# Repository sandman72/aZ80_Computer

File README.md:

# aZ80_Computer

#### Was ist der aZ80 Retro Computer?

Die Idee war: Wir bauen einen kleinen bezahlbaren Retro Computer für Workshops im Attraktor e.V.

 - Mit Steckkarten, damit man ihn erweitern kann. 
 - Beim Aufbau jeder Karte gibt es einen Einblick, was diese im Detail macht und wie sie funktioniert
 - Eine Einführung zur Computertechnik der 70er Jahre und die Gedankengänge und Evolutionen, die es zu der Zeit gab.
 - Wir programmieren auf dem aZ80 mit MS-BASIC und Assembler, z.B. kleine Spiele und Programme.

Unter Docs findet sich eine erste Präsentation über das Projekt. Eine ausführliche Anleitung folgt nach den ersten Workshops.

#### Hardware

Die Entscheidung was für ein System ich "neu" entwickeln wollte, fiel auf einen Bauvorschlag von <a href="http://searle.wales/">Grant Searle</a>, 
der auch bei einigen anderen Retro-Computern (z.B. RC2014) zum Einsatz kam. Damit gibt es eine gewisse 
Kompatibilität zum RC2014 System und den Steckkarten, aber der aZ80 sollte als Open-Hardware und -Software verfügbar 
sein und nicht hinter einer Paywall liegen, teure Kits oder Zusatz Hardware benötigen, z.B. wie der RC2014.

#### Software

Für den aZ80 wurden eine alte Version von MS Basic (Nascom Basic 4.7) und der Efex Monitor (Efex V4 1.0) mit einem eigenen BIOS kombiniert.
Das BIOS checkt, ob die wichtigsten Karten des Systems funktionieren und initialisiert diese. Danach erscheint über die serielle Schnittstelle
die Auswahlmöglichkeit zwischen dem Basic und dem Monitor Programm. Diese sind so angepasst, dass sie mit dem 
Online Z80 Compiler <a href="https://www.asm80.com/">ASM80</a> bearbeitet werden können.

Nascom Basic Verweis: <a href="https://gitlab.com/feilipu/NASCOM_BASIC"> https://gitlab.com/feilipu/NASCOM_BASIC </a>

Efex V4 1.0 Verweis: <a href="https://mkpeker.wixsite.com/efex"> https://mkpeker.wixsite.com/efex </a>

#### VDP

Als Highlight hat der aZ80 ein Video Display Prozessor mit an Board, der die Verbindung in die jetzige Zeit herstellt. Mit dieser Karte kann man den aZ80
an einen DVI/HDMI Monitor anschließen und per USB auch Tastatur, Maus, Joystick und/oder Speicher anschließen. Das kombiniert mit einem schicken Gehäuse
mit eingebautem Display gibt dann einen kleinen feinen Standalone Z80 Computer.

Der VDP wird über die serielle Schnittstelle angesprochen und kann Text 40x25 Zeichen oder auch Grafiken (320x240 Pixel mit 256 Farben), Sprites oder 
einen Mouse Cursor anzeigen. Zusätzlich gibt es einen Debug Bildschirm, mit dem man den aktuellen Status sich anzeigen lassen kann (Win+ESC Taste).

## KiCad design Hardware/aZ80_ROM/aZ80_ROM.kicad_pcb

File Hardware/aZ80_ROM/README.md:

# aZ80 ROM Platine

Die ROM Platine stellt dem aZ80 Retro System den nichtflüchtigen Speicher zur Verfügung. 

Der 32KB große Speicherbaustein (EEPROM) ist in 4 8KB große Teile (Bänke/Pages) aufgeteilt.

Das ROM wird im ersten Speicherbereich eingeblendet ($0000 - $3FFF) und enthält auch die Interrupt Vectoren.

#### Bank Auswahl

Über die Jumper JP1 und JP2 kann der 8KB Teil des ROMs eingestellt werden, der dem aZ80 zur Verfügung gestellt werden soll.

| JP2 | JP1 | Bank |
|:---:|:---:|:-----|
| 0 | 0 | 1 - BIOS mit BASIC und MONITOR |
| 0 | 1 | 2 - Diagnostic ROM |
| 1 | 0 | (aktuell Kopie von Bank 1) |
| 1 | 1 | (aktuell Kopie von Bank 2) |

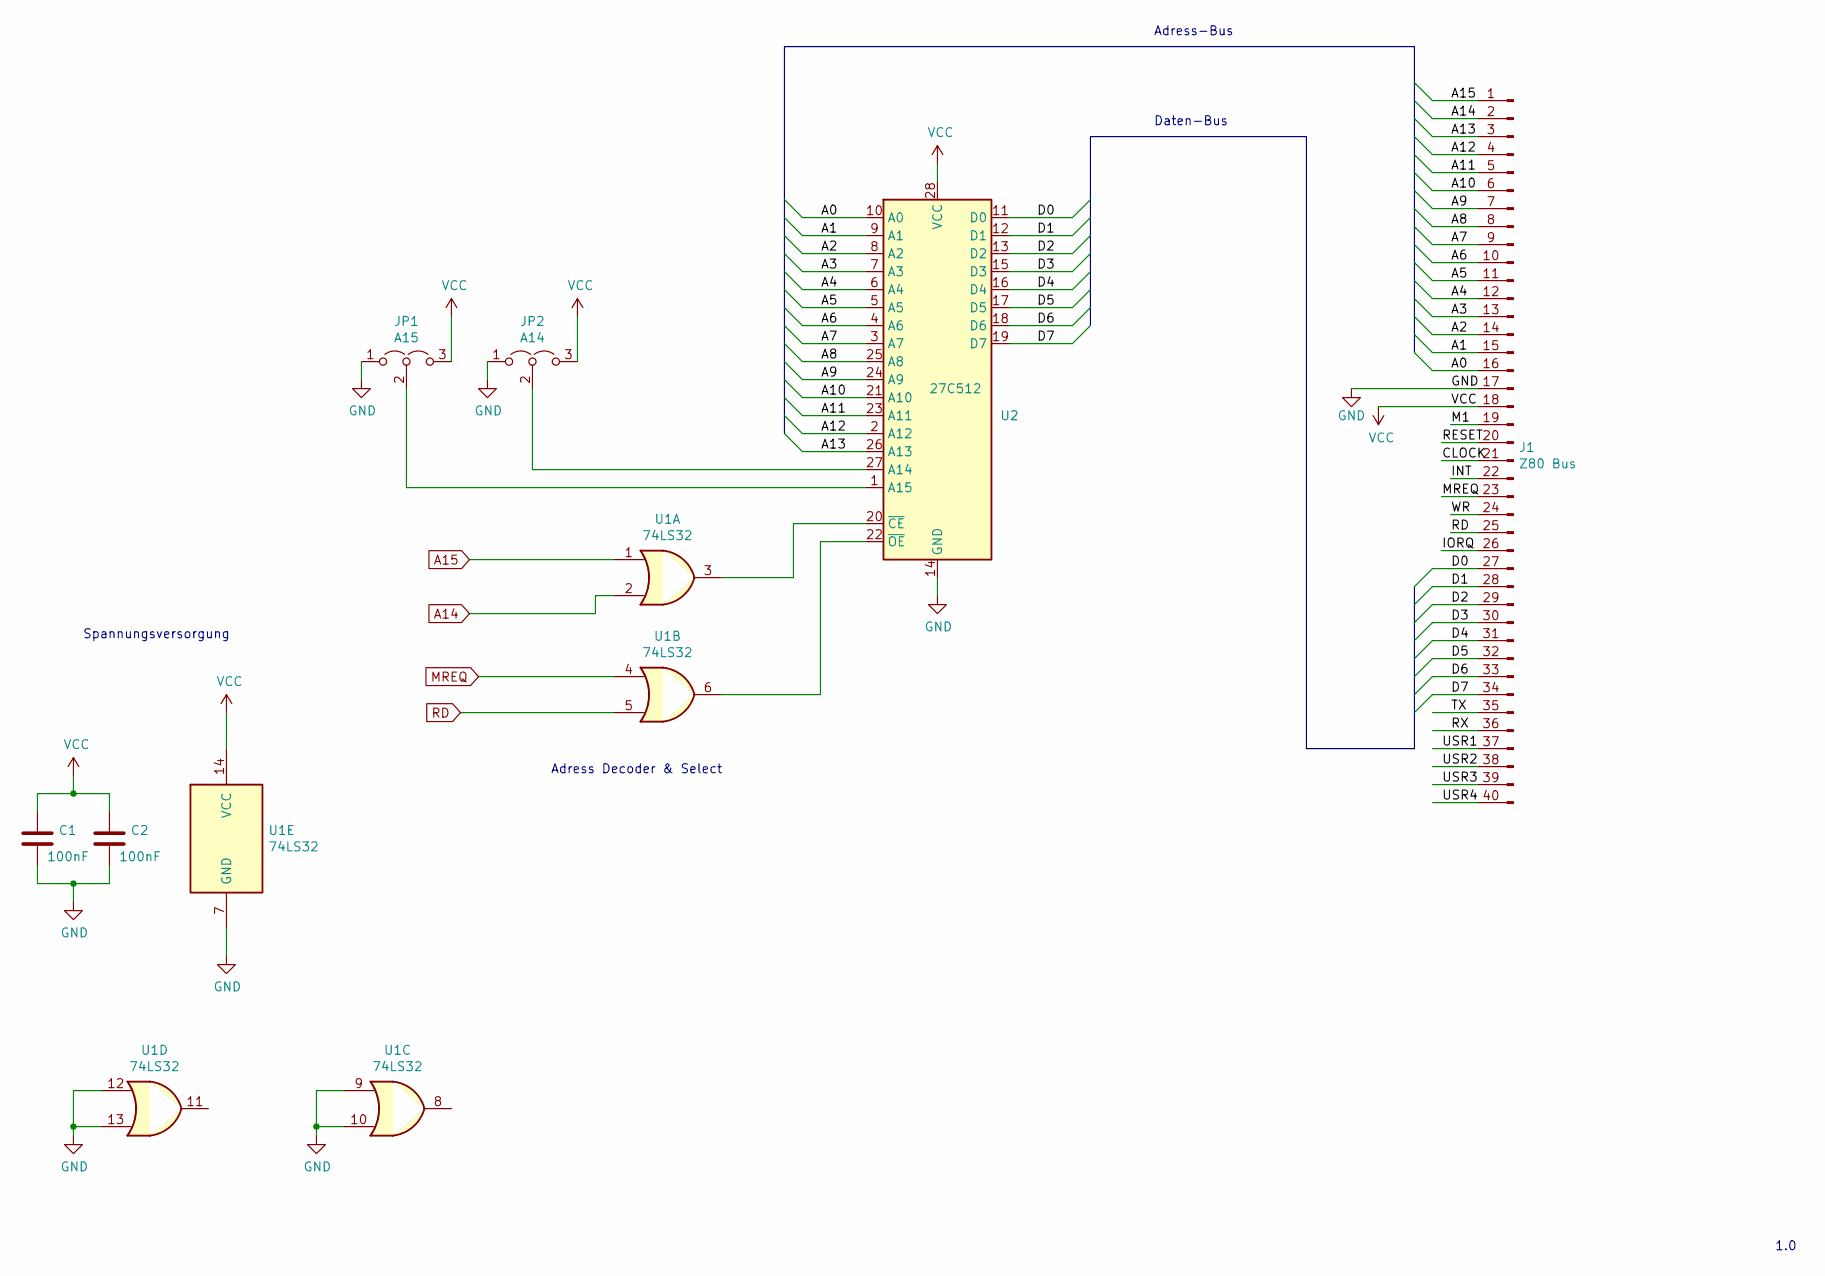
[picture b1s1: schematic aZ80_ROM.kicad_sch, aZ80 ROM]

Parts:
C1, C2: 100nF; C_Disc_D3.8mm_W2.6mm_P2.50mm
J1: Z80 Bus; PinHeader_1x40_P2.54mm_Horizontal
JP1: A15; PinHeader_1x03_P2.54mm_Vertical
JP2: A14; PinHeader_1x03_P2.54mm_Vertical
U1: 74LS32; DIP-14_W7.62mm_Socket_LongPads
U2: 27C512; DIP-28_W15.24mm_LongPads

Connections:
/A0: J1.16, U2.10 (A0)
/A1: J1.15, U2.9 (A1)
/A2: J1.14, U2.8 (A2)
/A3: J1.13, U2.7 (A3)
/A4: J1.12, U2.6 (A4)
/A5: J1.11, U2.5 (A5)
/A6: J1.10, U2.4 (A6)
/A7: J1.9, U2.3 (A7)
/A8: J1.8, U2.25 (A8)
/A9: J1.7, U2.24 (A9)
/A10: J1.6, U2.21 (A10)
/A11: J1.5, U2.23 (A11)
/A12: J1.4, U2.2 (A12)
/A13: J1.3, U2.26 (A13)
/CLOCK: J1.21
/D0: J1.27, U2.11 (D0)
/D1: J1.28, U2.12 (D1)
/D2: J1.29, U2.13 (D2)
/D3: J1.30, U2.15 (D3)
/D4: J1.31, U2.16 (D4)
/D5: J1.32, U2.17 (D5)
/D6: J1.33, U2.18 (D6)
/D7: J1.34, U2.19 (D7)
/INT: J1.22
/IORQ: J1.26
/M1: J1.19
/RESET: J1.20
/RX: J1.36
/TX: J1.35
/USR1: J1.37
/USR2: J1.38
/USR3: J1.39
/USR4: J1.40
/WR: J1.24
A14: J1.2, U1.2
A15: J1.1, U1.1
GND: C1.2, C2.2, J1.17, JP1.1 (A), JP2.1 (A), U1.7 (GND), U1.9, U1.10, U1.12, U1.13, U2.14 (GND)
MREQ: J1.23, U1.4
unnamed: JP1.2 (C), U2.1 (A15)
unnamed: JP2.2 (C), U2.27 (A14)
unnamed: U1.3, U2.20 (~CE)
unnamed: U1.6, U2.22 (~OE)
RD: J1.25, U1.5
VCC: C1.1, C2.1, J1.18, JP1.3 (B), JP2.3 (B), U1.14 (VCC), U2.28 (VCC)

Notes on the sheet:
Daten-Bus
Adress Decoder & Select
Adress-Bus
Spannungsversorgung
1.0

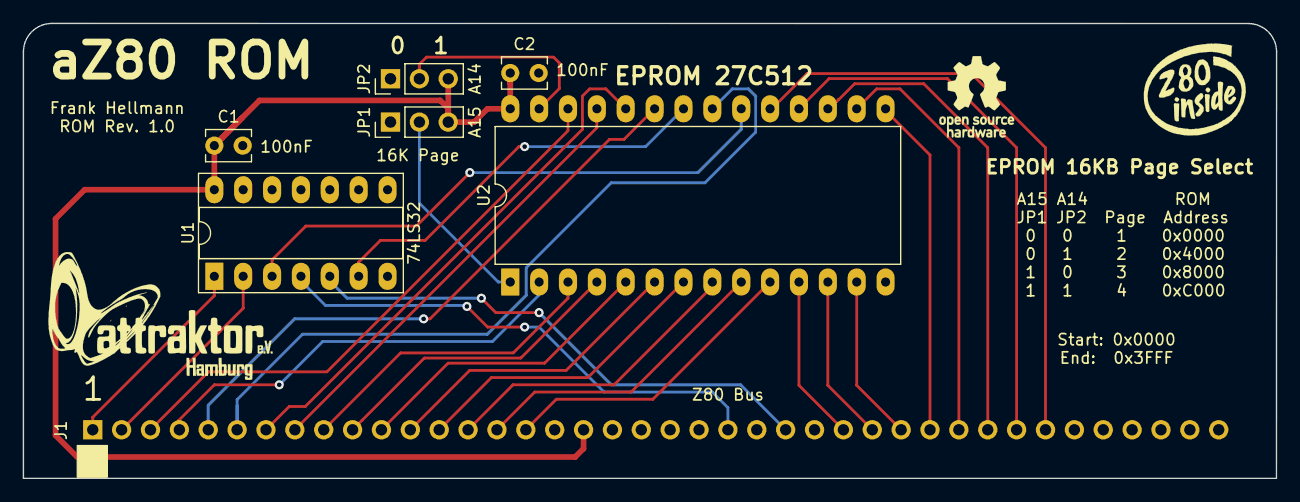
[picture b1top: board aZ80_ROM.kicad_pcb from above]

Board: 2 copper layers, 110.2 x 40.0 mm, 7 parts (1 on the bottom side), 32 nets.

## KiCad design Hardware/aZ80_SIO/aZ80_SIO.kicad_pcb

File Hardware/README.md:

# aZ80 Hardware

#### Wie funktioniert der aZ80 Retro Computer?

Wenn man sich die Teile dieses Computers, wie Bus-Platine, Taktgenerator, CPU, RAM, ROM, Serielle Schnittstelle usw., als Teile eines menschlichen Körpers vorstellt, dann wäre z.B. die Bus-Platine das Rückgrat, welche die anderen Komponenten verbindet. An der Busplatine hängt dann die Taktplatine, die den Herzschlag an allen Platinen liefert und diese damit synchronisiert. Die CPU als Hirn hängt genauso am Bus und verarbeitet alle Sinneseindrücke und gibt die Befehle. Die ROM und RAM Platinen hängen dort auch wie unser Gedächtnis mit am Bus. Und die Serielle Schnittstelle arbeitet wie unser Mund und Ohren und nimmt die Verständigung mit der Umwelt auf.

Alle Teile werden benötigt um ein funktionierenden Computer zu bekommen und wenn ein Teil nicht richtig funktioniert, kann sich das aZ80 System im übertragenen Sinne z.B. nichts merken, oder auch nicht richtig sprechen.

#### Aus welchen Komponenten besteht das aZ80 System?

Über die zentrale Verbindungsplatine (aZ80 Bus) werden die Prozessorplatine (aZ80 CPU),
der Festwertspeicher (aZ80 ROM), der Zugriffspeicher (aZ80 RAM), die Taktplatine (aZ80 Clock),
der serielle Controller (aZ80 Serial), die Ein- und Ausgabeplatine (aZ80 DIO) und weitere Platinen,
miteinander verbunden. Der 40 Pin breite Bus des aZ80 enthält die wichtigsten Signale um diese 
Komponenten miteinander zu verbinden. Weitere Infos und Produktionsdaten findet man im jeweiligen
Unterordner.

## Hier weitere Infos zur Hardware:

### Pin-Belegung der aZ80 Busses:

|   Pin   |  Signal  |
|--------:|:---------|
|  1 - 16 | A15-A0 	Adress-Bus | 
|      17 | GND		Masse |
|      18 | VCC +5V	Versorgungsspannung |
|      19 | M1		Steuerungssignal |
|      20 | RESET		Zurücksetzen des Systems |
|      21 | CLOCK		Taktsignal 3,68MHz |
|      22 | INT		Interrupt, Unterbrechungsanforderung |
|      23 | MREQ		Memory Request, Speicheranfrage |
|      24 | WR		Write, Daten schreiben |
|      25 | RD		Read, Daten lesen |
|      26 | IORQ		I/O Request, I/O-Anfrage |
| 27 - 34 | D0-D7		Daten-Bus |
|      35 | TX		Serielle Daten Senden |
|      36 | RX		Serielle Daten Empfangen |
| 37 - 40 | USR1-USR4	Benutzerdefinierte Signale |  

### Speicher und I/O Adressen

#### ROM:  $0000 - $3FFF
|  Addresse  | Verwendung |
| ----------:|:-----------|
| $0000 | RST Vectors und System Funktionen |
| $0070 | BIOS |
| $0200 | BASIC |
| $2000 | MONITOR |
|   |   |
| $4000 - $7FFF	| Expansion ROM or VideoRAM 16K (preliminary) |

#### RAM:  $8000 - $FFFF
|  Addresse  | Verwendung |
| ----------:|:-----------|
| $8000 - $80FF | System Variables (Zero Page) |
|   $8000 | Serial Buffer  size $3F |
|   $8040 | Serial In Pointer  size 2 |
|   $8042 | Serial Rd Pointer  size 2 |
|   $8044 | Serial Buffer Used	size 2 |
|   $8046 | Basic Started?  size 1 |
| Init: | | 
|   $80ED | Temp Stack |			
| Basic: | |
|   $8047 | Workspace Start (see Basic) |
|   $81A3 | Basic Memory Start |
| Monitor: | |
|   $8047 | Workspace Start (see Monitor) |
| | |
| $8100 - $FFFF	| Stack + User Memory |

#### I/O Map
|  I/O Addresse  | Verwendung |
| -------------:|:-----------|
| $00-$0F	| Digital I/O 00000000 - 0000xx11  (preliminary) |
| $10-$1F	| IDE/CF  I/O 0001xx00 - 0001xx11  (preliminary) |
| $80-$81	| Serial  I/O 10xxxxx0 - 10xxxxx1  (addr decoder verbrät viele Addressen) |
| $C0-$CF	| Video   I/O 1100xx00 - 1100xx11  (preliminary) |
| $D0-$DF	| Audio   I/O 1101xx00 - 1101xx11  (preliminary) |

#### RST Vectors
|  Reset Vector | Verwendung |
| -------------:|:-----------|
| RST00		| $0000	Reset Vector |
| RST08		| $0008	TX Char - Sende Zeichen über seriellen Port |
| RST10		| $0010	RX Char - Empfange Zeichen über seriellen Port | 
| RST18		| $0018	Check Char - Überprüfe ob Zeichen eingegangen sind |
| RST20		| $0020	- |
| RST28		| $0028	- |
| RST30		| $0030	- |
| RST38		| $0038	INT Vector - |

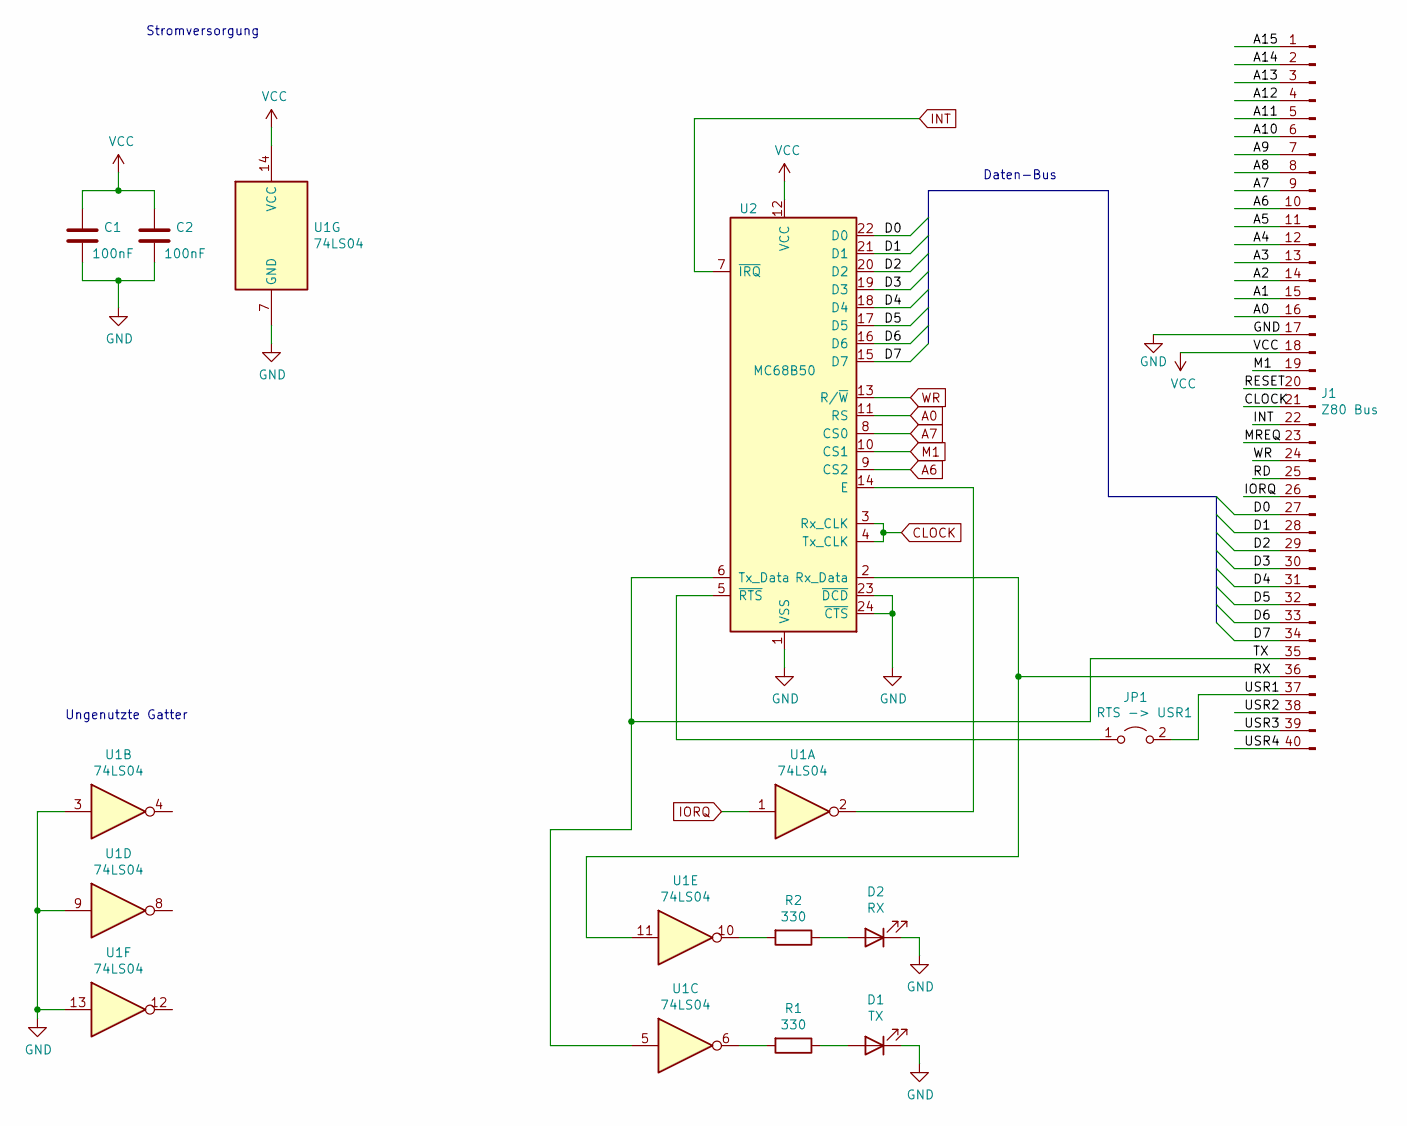
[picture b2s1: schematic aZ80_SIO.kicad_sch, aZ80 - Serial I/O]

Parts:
C1, C2: 100nF; C_Disc_D3.8mm_W2.6mm_P2.50mm
D1: TX; LED_D5.0mm
D2: RX; LED_D5.0mm
J1: Z80 Bus; PinHeader_1x40_P2.54mm_Horizontal
JP1: RTS -> USR1; PinSocket_1x02_P2.54mm_Vertical
R1, R2: 330; R_Axial_DIN0207_L6.3mm_D2.5mm_P10.16mm_Horizontal
U1: 74LS04; DIP-14_W7.62mm_Socket_LongPads
U2: MC68B50; DIP-24_W15.24mm_Socket_LongPads

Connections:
/A1: J1.15
/A2: J1.14
/A3: J1.13
/A4: J1.12
/A5: J1.11
/A8: J1.8
/A9: J1.7
/A10: J1.6
/A11: J1.5
/A12: J1.4
/A13: J1.3
/A14: J1.2
/A15: J1.1
/D0: J1.27, U2.22 (D0)
/D1: J1.28, U2.21 (D1)
/D2: J1.29, U2.20 (D2)
/D3: J1.30, U2.19 (D3)
/D4: J1.31, U2.18 (D4)
/D5: J1.32, U2.17 (D5)
/D6: J1.33, U2.16 (D6)
/D7: J1.34, U2.15 (D7)
/MREQ: J1.23
/RD: J1.25
/RESET: J1.20
/RX: J1.36, U1.11, U2.2 (Rx_Data)
/TX: J1.35, U1.5, U2.6 (Tx_Data)
/USR1: J1.37, JP1.2 (B)
/USR2: J1.38
/USR3: J1.39
/USR4: J1.40
A0: J1.16, U2.11 (RS)
A6: J1.10, U2.9 (CS2)
A7: J1.9, U2.8 (CS0)
CLOCK: J1.21, U2.3 (Rx_CLK), U2.4 (Tx_CLK)
GND: C1.2, C2.2, D1.1 (K), D2.1 (K), J1.17, U1.3, U1.7 (GND), U1.9, U1.13, U2.1 (VSS), U2.23 (~DCD), U2.24 (~CTS)
INT: J1.22, U2.7 (~IRQ)
IORQ: J1.26, U1.1
M1: J1.19, U2.10 (CS1)
unnamed: D1.2 (A), R1.1
unnamed: D2.2 (A), R2.1
unnamed: JP1.1 (A), U2.5 (~RTS)
unnamed: R1.2, U1.6
unnamed: R2.2, U1.10
unnamed: U1.2, U2.14 (E)
VCC: C1.1, C2.1, J1.18, U1.14 (VCC), U2.12 (VCC)
WR: J1.24, U2.13 (R/~W)

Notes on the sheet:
Daten-Bus
Ungenutzte Gatter
Stromversorgung

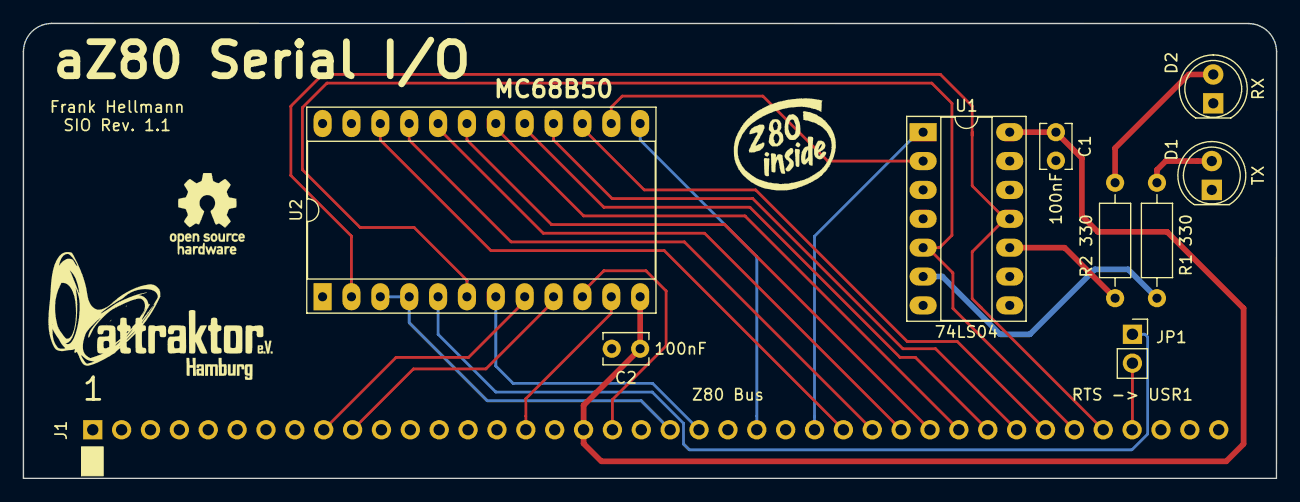
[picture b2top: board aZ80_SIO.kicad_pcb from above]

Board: 2 copper layers, 110.2 x 40.0 mm, 10 parts (1 on the bottom side), 27 nets.

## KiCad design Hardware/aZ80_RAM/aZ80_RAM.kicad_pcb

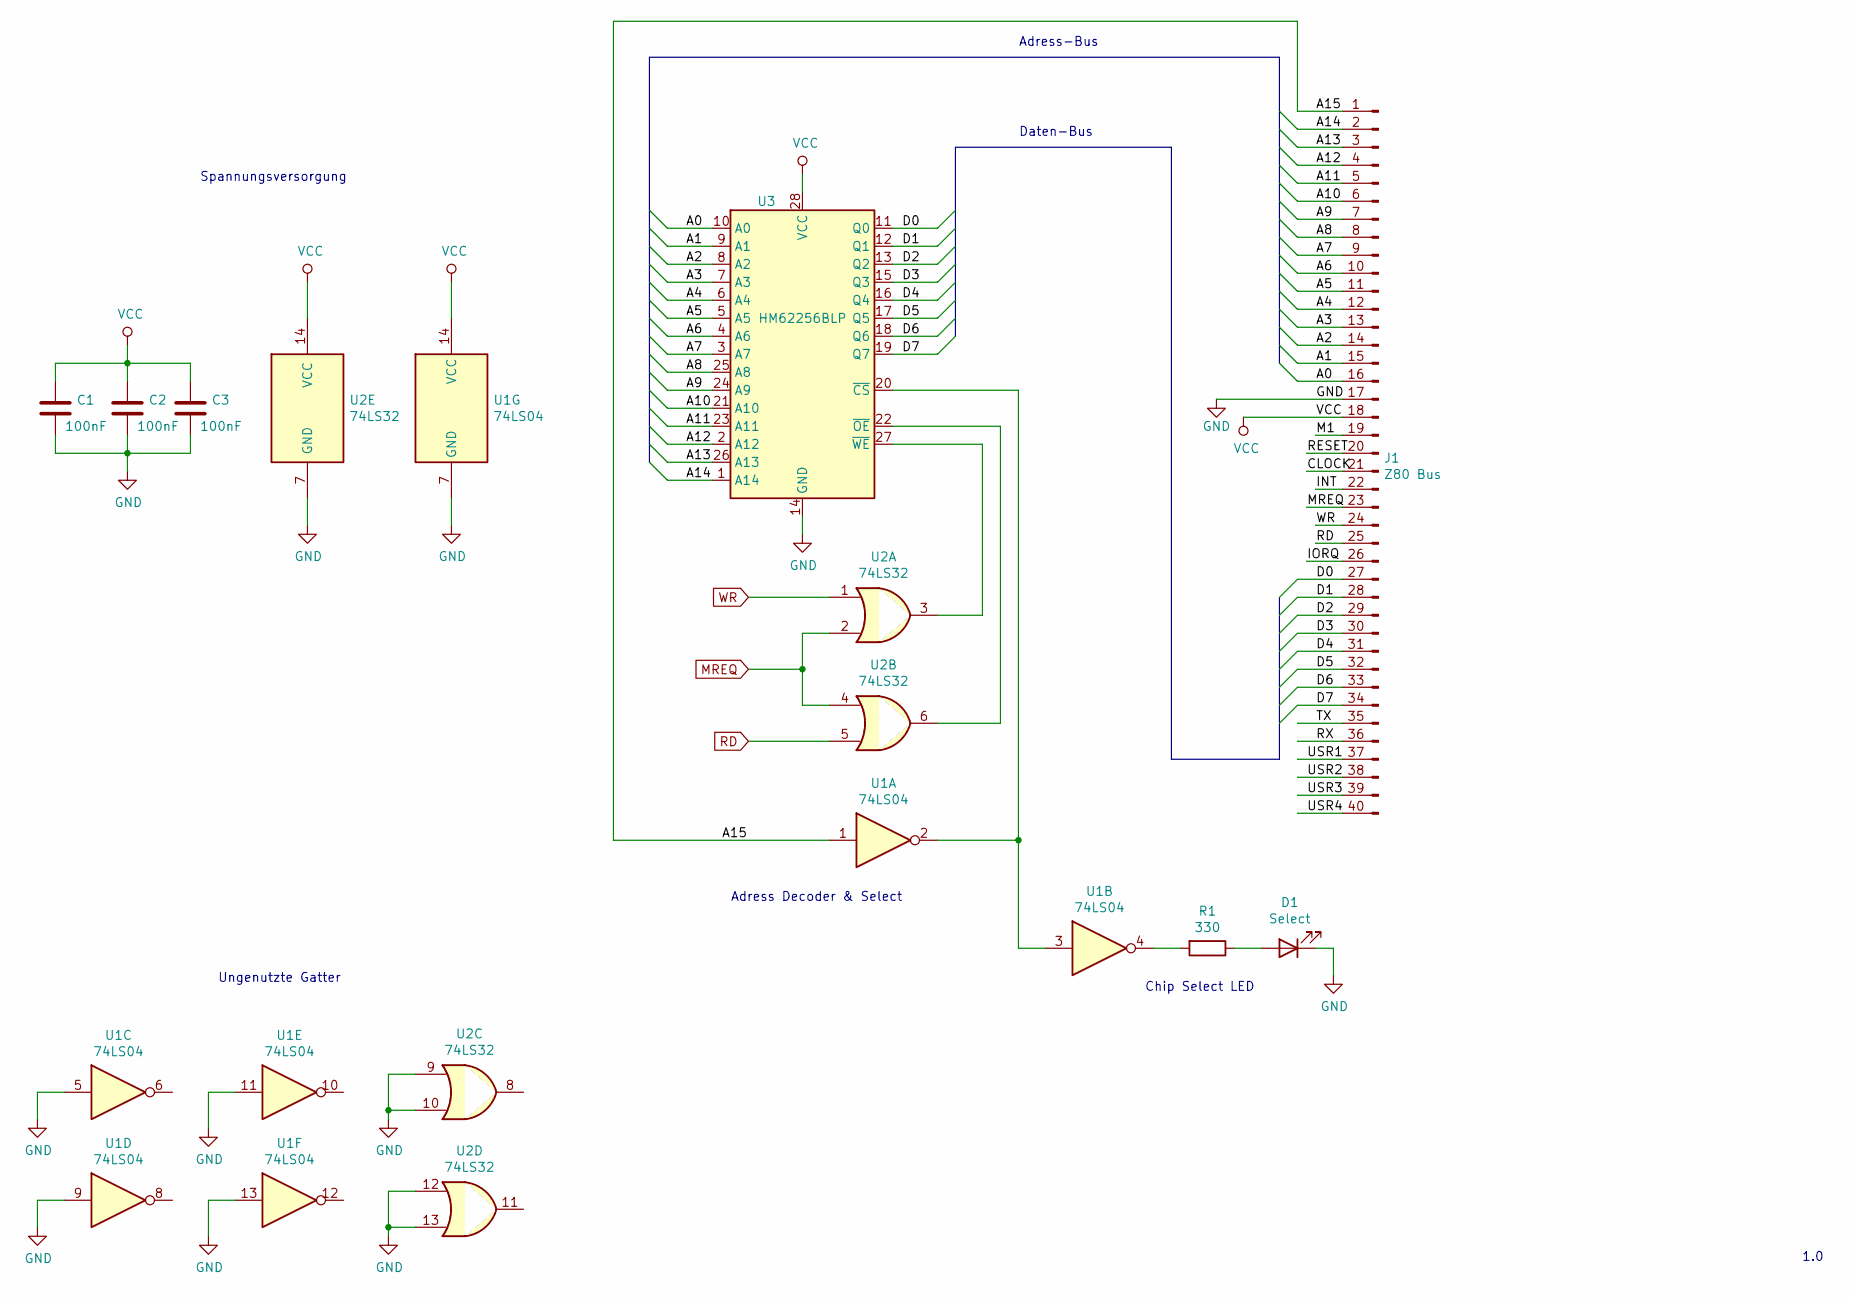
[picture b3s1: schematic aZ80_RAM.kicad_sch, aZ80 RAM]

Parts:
C1, C2, C3: 100nF; C_Disc_D3.8mm_W2.6mm_P2.50mm
D1: Select; LED_D5.0mm
J1: Z80 Bus; PinHeader_1x40_P2.54mm_Horizontal
R1: 330; R_Axial_DIN0207_L6.3mm_D2.5mm_P10.16mm_Horizontal
U1: 74LS04; DIP-14_W7.62mm_Socket_LongPads
U2: 74LS32; DIP-14_W7.62mm_Socket_LongPads
U3: HM62256BLP; DIP-28_W15.24mm_LongPads

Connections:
/A0: J1.16, U3.10 (A0)
/A1: J1.15, U3.9 (A1)
/A2: J1.14, U3.8 (A2)
/A3: J1.13, U3.7 (A3)
/A4: J1.12, U3.6 (A4)
/A5: J1.11, U3.5 (A5)
/A6: J1.10, U3.4 (A6)
/A7: J1.9, U3.3 (A7)
/A8: J1.8, U3.25 (A8)
/A9: J1.7, U3.24 (A9)
/A10: J1.6, U3.21 (A10)
/A11: J1.5, U3.23 (A11)
/A12: J1.4, U3.2 (A12)
/A13: J1.3, U3.26 (A13)
/A14: J1.2, U3.1 (A14)
/A15: J1.1, U1.1
/CLOCK: J1.21
/D0: J1.27, U3.11 (Q0)
/D1: J1.28, U3.12 (Q1)
/D2: J1.29, U3.13 (Q2)
/D3: J1.30, U3.15 (Q3)
/D4: J1.31, U3.16 (Q4)
/D5: J1.32, U3.17 (Q5)
/D6: J1.33, U3.18 (Q6)
/D7: J1.34, U3.19 (Q7)
/INT: J1.22
/IORQ: J1.26
/M1: J1.19
/RESET: J1.20
/RX: J1.36
/TX: J1.35
/USR1: J1.37
/USR2: J1.38
/USR3: J1.39
/USR4: J1.40
GND: C1.2, C2.2, C3.2, D1.1 (K), J1.17, U1.5, U1.7 (GND), U1.9, U1.11, U1.13, U2.7 (GND), U2.9, U2.10, U2.12, U2.13, U3.14 (GND)
MREQ: J1.23, U2.2, U2.4
unnamed: D1.2 (A), R1.1
unnamed: R1.2, U1.4
unnamed: U1.2, U1.3, U3.20 (~CS)
unnamed: U2.3, U3.27 (~WE)
unnamed: U2.6, U3.22 (~OE)
RD: J1.25, U2.5
VCC: C1.1, C2.1, C3.1, J1.18, U1.14 (VCC), U2.14 (VCC), U3.28 (VCC)
WR: J1.24, U2.1

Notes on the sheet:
Daten-Bus
Ungenutzte Gatter
Adress-Bus
Chip Select LED
1.0
Spannungsversorgung
Adress Decoder & Select

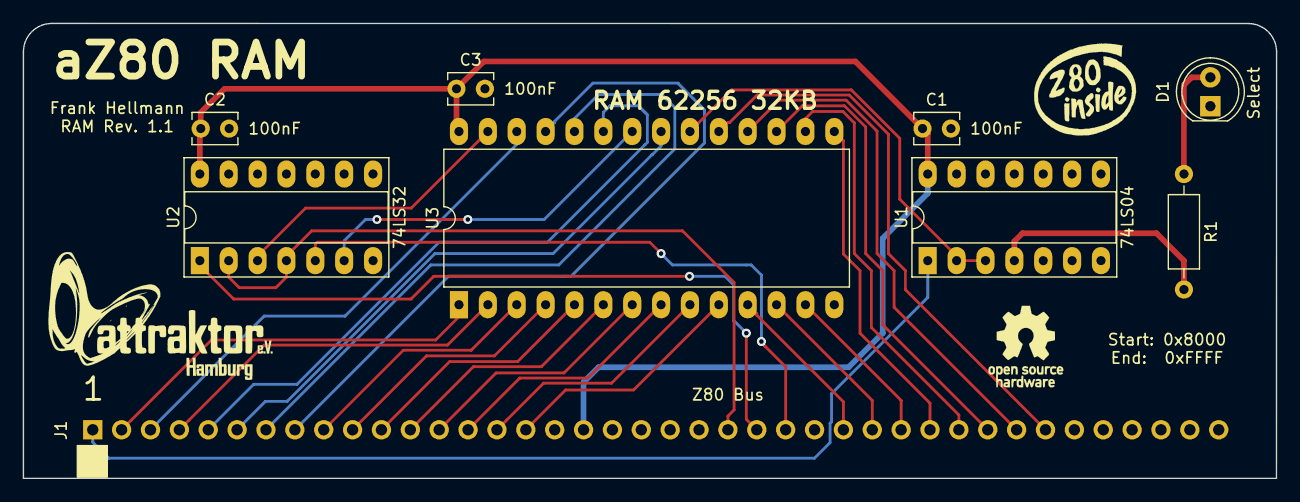
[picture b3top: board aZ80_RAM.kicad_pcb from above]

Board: 2 copper layers, 110.2 x 40.0 mm, 9 parts (1 on the bottom side), 34 nets.

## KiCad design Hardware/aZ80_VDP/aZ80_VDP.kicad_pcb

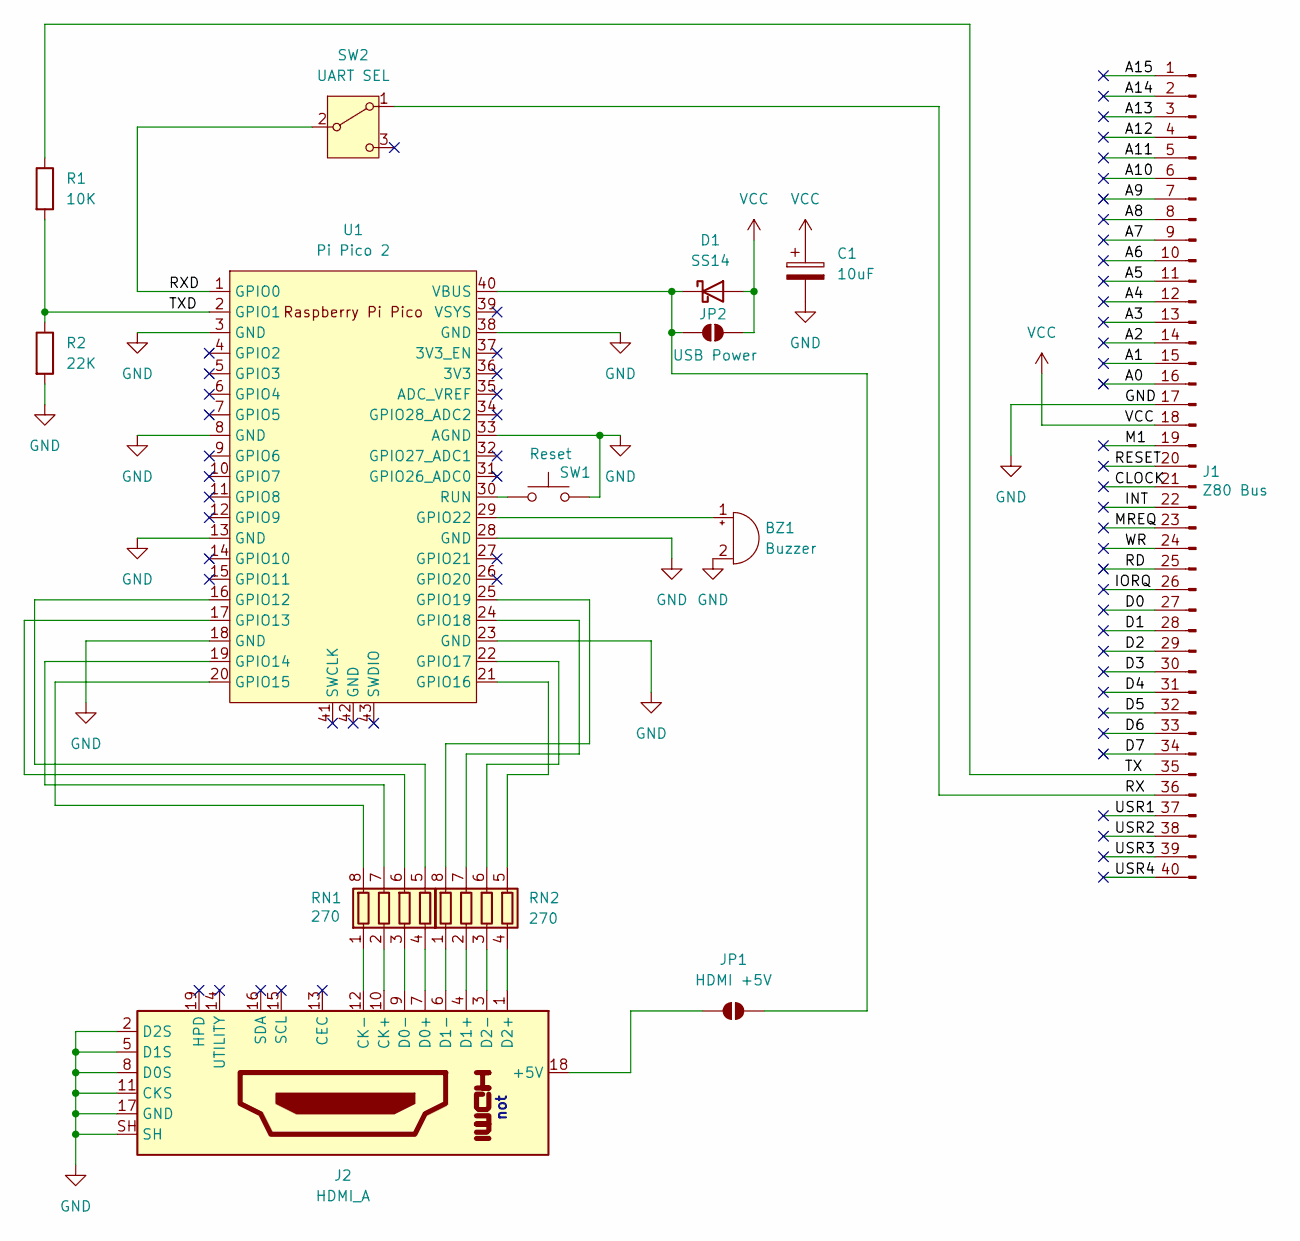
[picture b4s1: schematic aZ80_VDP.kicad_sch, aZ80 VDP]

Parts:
BZ1: Buzzer; Buzzer_12x9.5RM7.6
C1: 10uF; CP_Elec_4x5.7
D1: SS14; D_SMA
J1: Z80 Bus; PinHeader_1x40_P2.54mm_Horizontal
J2: HDMI_A; HDMI_A_Molex_208658-1001_Horizontal
JP1: HDMI +5V; SolderJumper-2_P1.3mm_Open_RoundedPad1.0x1.5mm
JP2: USB Power; SolderJumper-2_P1.3mm_Open_RoundedPad1.0x1.5mm
R1: 10K; R_0603_1608Metric
R2: 22K; R_0603_1608Metric
RN1, RN2: 270; R_Array_Convex_4x0603
SW1: Reset; SW_Push_1P1T_NO_6x6mm_H9.5mm
SW2: UART SEL; SW_Slide_SPDT_Angled_CK_OS102011MA1Q
U1: Pi Pico 2; RPi_Pico_SMD_TH

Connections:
/A0: J1.16
/A1: J1.15
/A2: J1.14
/A3: J1.13
/A4: J1.12
/A5: J1.11
/A6: J1.10
/A7: J1.9
/A8: J1.8
/A9: J1.7
/A10: J1.6
/A11: J1.5
/A12: J1.4
/A13: J1.3
/A14: J1.2
/A15: J1.1
/CLOCK: J1.21
/D0: J1.27
/D1: J1.28
/D2: J1.29
/D3: J1.30
/D4: J1.31
/D5: J1.32
/D6: J1.33
/D7: J1.34
/INT: J1.22
/IORQ: J1.26
/M1: J1.19
/MREQ: J1.23
/RD: J1.25
/RESET: J1.20
/RX: J1.36, SW2.1 (A); also elsewhere on the board
/RXD: SW2.2 (B), U1.1 (GPIO0); also elsewhere on the board
/TX: J1.35, R1.1
/TXD: R1.2, R2.1, U1.2 (GPIO1)
/USR1: J1.37
/USR2: J1.38
/USR3: J1.39
/USR4: J1.40
/WR: J1.24
GND: BZ1.2 (-), C1.2, J1.17, J2.2 (D2S), J2.5 (D1S), J2.8 (D0S), J2.11 (CKS), J2.17 (GND), J2.SH, R2.2, SW1.2, U1.3 (GND), U1.8 (GND), U1.13 (GND), U1.18 (GND), U1.23 (GND), U1.28 (GND), U1.33 (AGND), U1.38 (GND)
unnamed: BZ1.1 (+), U1.29 (GPIO22)
unnamed: D1.1 (K), JP1.2 (B), JP2.1 (A), U1.40 (VBUS)
unnamed: J2.18 (+5V), JP1.1 (A)
unnamed: J2.10 (CK+), RN1.2 (R2.1)
unnamed: J2.12 (CK-), RN1.1 (R1.1)
unnamed: J2.7 (D0+), RN1.4 (R4.1)
unnamed: J2.9 (D0-), RN1.3 (R3.1)
unnamed: J2.4 (D1+), RN2.2 (R2.1)
unnamed: J2.6 (D1-), RN2.1 (R1.1)
unnamed: J2.1 (D2+), RN2.4 (R4.1)
unnamed: J2.3 (D2-), RN2.3 (R3.1)
unnamed: RN1.8 (R1.2), U1.20 (GPIO15)
unnamed: RN1.7 (R2.2), U1.19 (GPIO14)
unnamed: RN1.6 (R3.2), U1.17 (GPIO13)
unnamed: RN1.5 (R4.2), U1.16 (GPIO12)
unnamed: RN2.8 (R1.2), U1.25 (GPIO19)
unnamed: RN2.7 (R2.2), U1.24 (GPIO18)
unnamed: RN2.6 (R3.2), U1.22 (GPIO17)
unnamed: RN2.5 (R4.2), U1.21 (GPIO16)
unnamed: SW1.1, U1.30 (RUN)
VCC: C1.1, D1.2 (A), J1.18, JP2.2 (B)

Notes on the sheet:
not

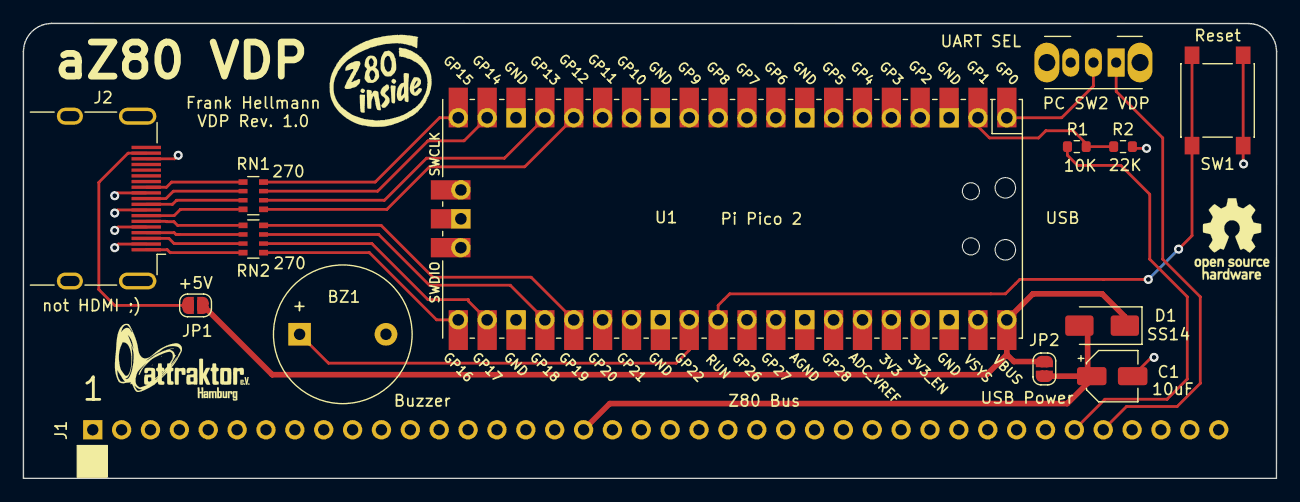
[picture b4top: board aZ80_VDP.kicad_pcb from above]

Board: 2 copper layers, 110.2 x 40.0 mm, 14 parts (1 on the bottom side), 26 nets.

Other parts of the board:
PC SW2 VDP: UART SEL; SW_Slide_SPDT_Angled_CK_OS102011MA1Q

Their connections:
/RX: PC SW2 VDP.1 (A); also elsewhere on the board
/RXD: PC SW2 VDP.2 (B); also elsewhere on the board

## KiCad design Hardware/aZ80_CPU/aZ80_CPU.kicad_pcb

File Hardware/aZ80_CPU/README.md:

# aZ80 CPU Platine

Die CPU Platine ist das Hirn des aZ80 Retro Computers und verarbeitet die Daten.

#### Switch USR -> CPU

Der Switch ist normalerweise in allen Positionen auf Off gestellt und erlaubt in Zukunft weiteren Karten die Steuerung der CPU.

 - 1 - WAIT 
 - 2 - NMI
 - 3 - BUSRQ
 - 4 - BUSAK

Das WAIT Signal hält die CPU an und wird aktuell nur beim Betrieb der SN76489 Soundkarte genutzt. Diese ist so langsam, dass sie die CPU anhalten muss, bis der nächste Befehl gesendet werden darf.

Das NMI (Non-Maskable-Interrupt) Signal ist aktuell ungenutzt.

Das BUSRQ (Bus-Request) Signal ist aktuell ungenutzt.

Das BUSAK (Bus-Acknowledge) Signal ist aktuell ungenutzt.

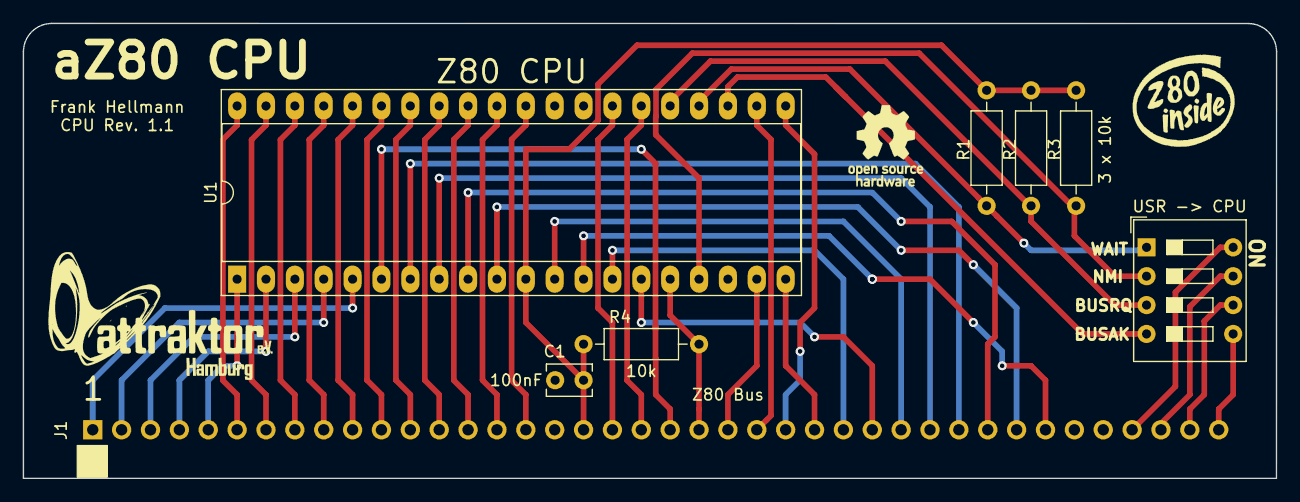
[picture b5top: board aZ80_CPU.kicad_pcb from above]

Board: 2 copper layers, 110.2 x 40.0 mm, 8 parts (1 on the bottom side), 42 nets.

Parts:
C1: 100nF; C_Disc_D3.8mm_W2.6mm_P2.50mm
J1: Z80 Bus; PinHeader_1x40_P2.54mm_Horizontal
R1, R2, R4: 10k; R_Axial_DIN0207_L6.3mm_D2.5mm_P10.16mm_Horizontal
R3: 3 x 10k; R_Axial_DIN0207_L6.3mm_D2.5mm_P10.16mm_Horizontal
U1: Z80CPU; DIP-40_W15.24mm_Socket_LongPads
USR -> CPU: Select USR; SW_DIP_SPSTx04_Slide_9.78x12.34mm_W7.62mm_P2.54mm

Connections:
/A0: J1.16, U1.30
/A1: J1.15, U1.31
/A2: J1.14, U1.32
/A3: J1.13, U1.33
/A4: J1.12, U1.34
/A5: J1.11, U1.35
/A6: J1.10, U1.36
/A7: J1.9, U1.37
/A8: J1.8, U1.38
/A9: J1.7, U1.39
/A10: J1.6, U1.40
/A11: J1.5, U1.1
/A12: J1.4, U1.2
/A13: J1.3, U1.3
/A14: J1.2, U1.4
/A15: J1.1, U1.5
/CLOCK: J1.21, U1.6
/D0: J1.27, U1.14
/D1: J1.28, U1.15
/D2: J1.29, U1.12
/D3: J1.30, U1.8
/D4: J1.31, U1.7
/D5: J1.32, U1.9
/D6: J1.33, U1.10
/D7: J1.34, U1.13
/IORQ: J1.26, U1.20
/M1: J1.19, U1.27
/MREQ: J1.23, U1.19
/RD: J1.25, U1.21
/RESET: J1.20, U1.26
/USR1: J1.37, USR -> CPU.8
/USR2: J1.38, USR -> CPU.7
/USR3: J1.39, USR -> CPU.6
/USR4: J1.40, USR -> CPU.5
/WR: J1.24, U1.22
BUSAK: U1.23, USR -> CPU.4
BUSRQ: R2.2, U1.25, USR -> CPU.3
GND: C1.2, J1.17, U1.29
INT: J1.22, R4.2, U1.16
NMI: R3.2, U1.17, USR -> CPU.2
VCC: C1.1, J1.18, R1.1, R2.1, R3.1, R4.1, U1.11
WAIT: R1.2, U1.24, USR -> CPU.1
